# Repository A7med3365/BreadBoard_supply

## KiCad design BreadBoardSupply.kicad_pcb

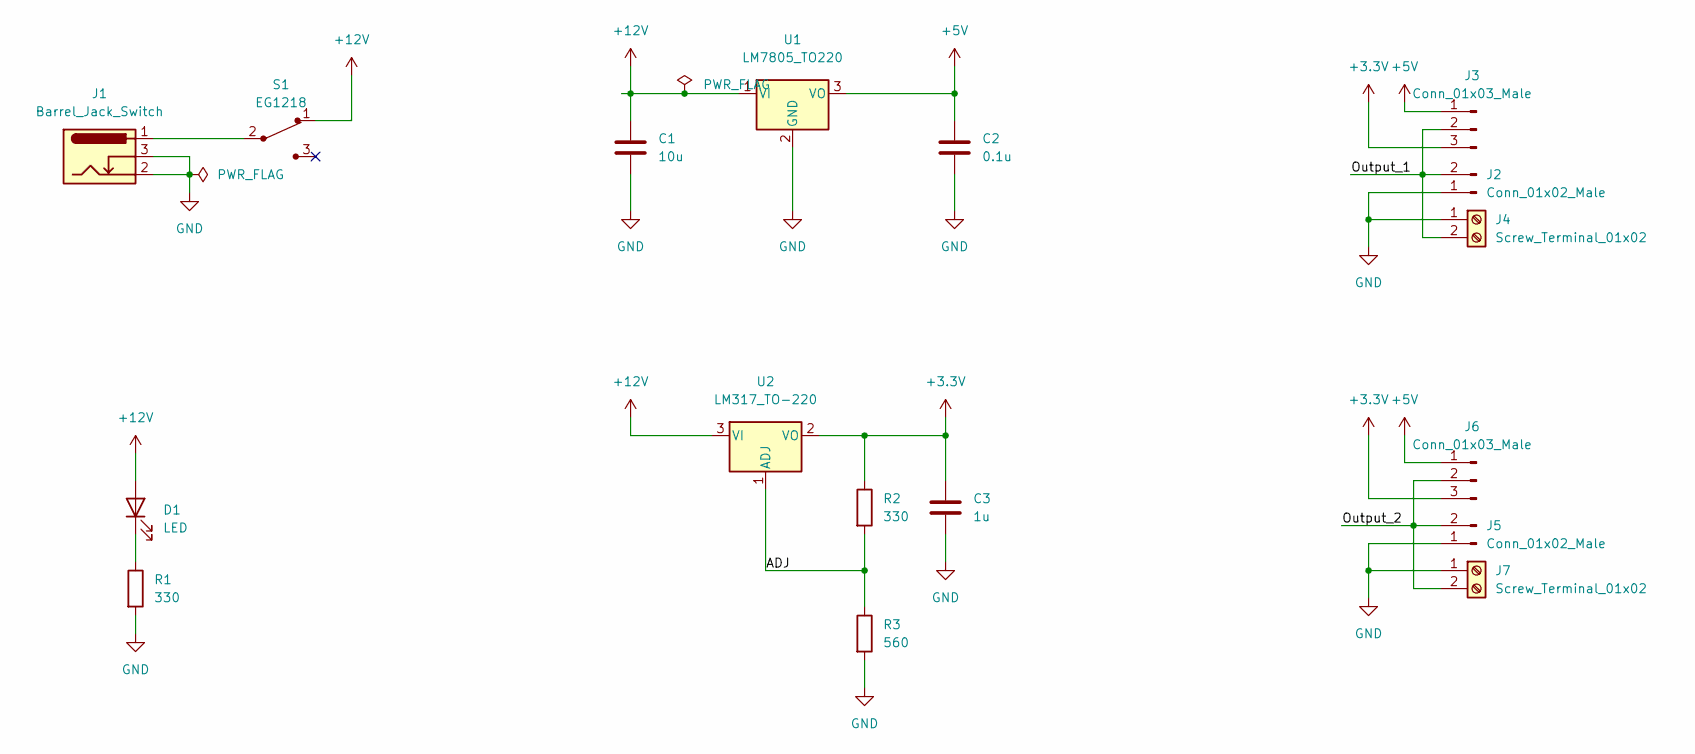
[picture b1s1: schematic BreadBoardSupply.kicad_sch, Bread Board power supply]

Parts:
C1: 10u; C_Disc_D3.0mm_W1.6mm_P2.50mm
C2: 0.1u; C_Disc_D3.0mm_W1.6mm_P2.50mm
C3: 1u; C_Disc_D3.0mm_W1.6mm_P2.50mm
D1: LED; LED_D3.0mm
J1: Barrel_Jack_Switch; BarrelJack_Horizontal
J2, J5: Conn_01x02_Male; PinHeader_1x02_P2.54mm_Vertical
J3, J6: Conn_01x03_Male; PinHeader_1x03_P2.54mm_Vertical
J4, J7: Screw_Terminal_01x02; TerminalBlock_bornier-2_P5.08mm
R1, R2: 330; R_Axial_DIN0204_L3.6mm_D1.6mm_P7.62mm_Horizontal
R3: 560; R_Axial_DIN0204_L3.6mm_D1.6mm_P7.62mm_Horizontal
S1: EG1218; Switch_Slide_11.6x4mm_EG1218; MPN EG1218; Digi-Key_PN EG1903-ND
U1: LM7805_TO220; TO-220-3_Vertical
U2: LM317_TO-220; TO-220-3_Vertical

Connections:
+3.3V: C3.1, J3.3, J6.3, R2.1, U2.2 (VO)
+5V: C2.1, J3.1, J6.1, U1.3 (VO)
+12V: C1.1, D1.2 (A), S1.1, U1.1 (VI), U2.3 (VI)
/ADJ: R2.2, R3.1, U2.1 (ADJ)
/Output_1: J2.2, J3.2, J4.2
/Output_2: J5.2, J6.2, J7.2
GND: C1.2, C2.2, C3.2, J1.2, J1.3, J2.1, J4.1, J5.1, J7.1, R1.2, R3.2, U1.2 (GND)
unnamed: D1.1 (K), R1.1
unnamed: J1.1, S1.2

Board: 2 copper layers, 17 parts (0 on the bottom side), 9 nets, no tracks yet.

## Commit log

2023-01-11 first commit, through hole components
2023-01-11 changed the footprints of some components, modified the regulator circuit
2023-01-11 not done but added some essential parts for the microUSB port
